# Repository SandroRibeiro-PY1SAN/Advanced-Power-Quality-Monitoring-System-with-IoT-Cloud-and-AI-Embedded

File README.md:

# Advanced-Power-Quality-Monitoring-System-with-IoT-Cloud-and-AI-Embedded
Authors:

Sandro Carneiro Ribeiro

Leonardo de Carvalho Vidal

-------------------------------------------------------------------------------------------------------------------------------------------
Real-time analyzer for managing the electrical variables of an installation connected to a power distributor. This equipment consists of several modular hardware modules and dedicated software.
This project has an electronic interface to support auxiliary voltage (J1) and current (J2) measurement boards, and the microcontroller (U2). The electrical design was developed using KiCad software version 8.0.

The microcontroller used is a 30-pin ESP-WROOM32 from Espressif. This model features the Xtensa® Dual-Core 32-bit LX6 microprocessor, with a maximum clock speed of 240 MHz, 520 KBytes of RAM and 4 MB of Flash memory, a 12-bit ADC, and Wi-Fi and Bluetooth Low Energy (BLE) 4.2 connectivity.

The designed board used 12-bit analog ADC inputs to receive signals from the voltage and current acquisition boards from the mains. Other inputs were reserved for future expansions.

MainBoard SCH:

MainBoard PCB Top:

MainBoard PCB Botton:

VAC Probe:

ACA Probe:

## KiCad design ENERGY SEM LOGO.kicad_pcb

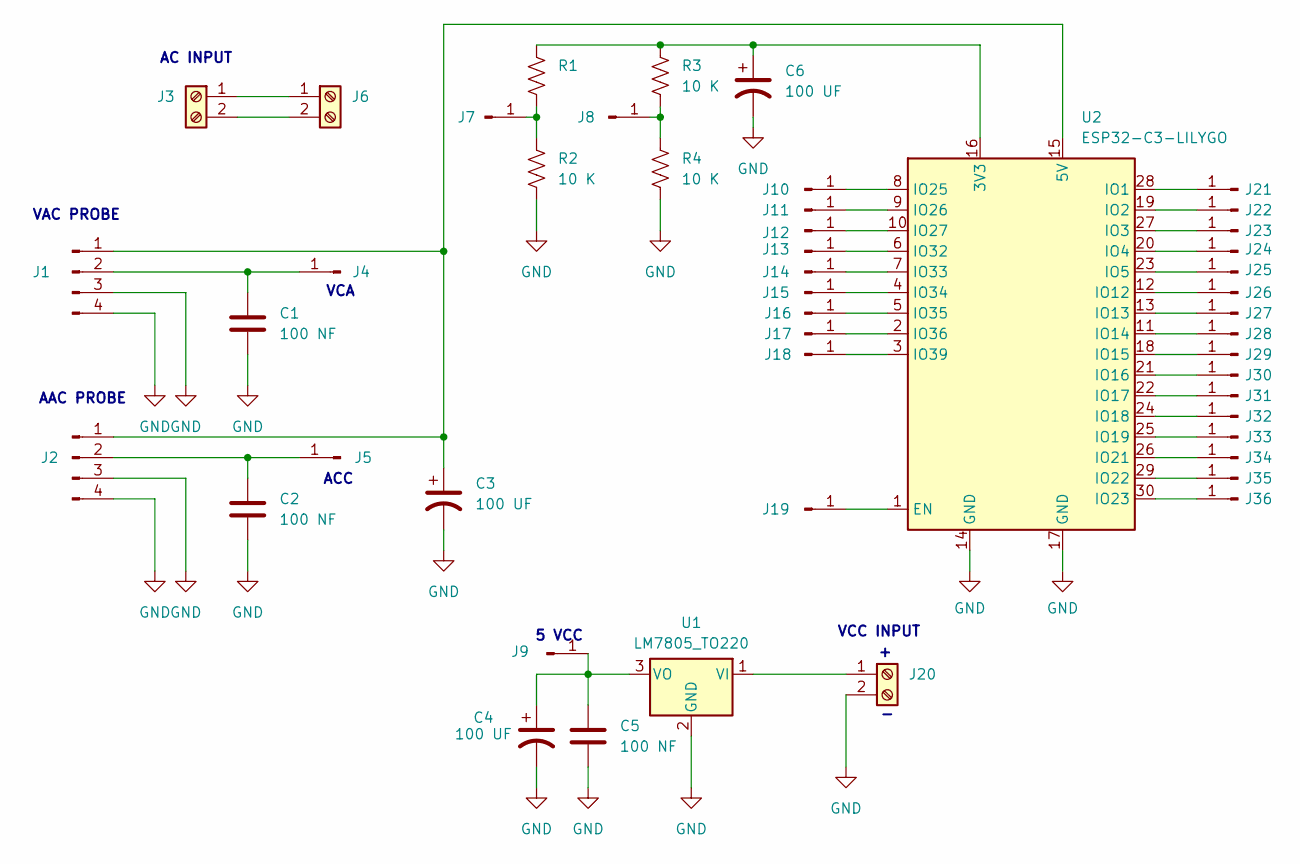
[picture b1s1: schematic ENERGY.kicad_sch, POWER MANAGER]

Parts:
C1, C2, C5: 100 NF; C_Disc_D10.5mm_W5.0mm_P7.50mm
C3, C4, C6: 100 UF; CP_Radial_D8.0mm_P5.00mm
J1, J2: Conn_01x04_Pin; FanPinHeader_1x04_P2.54mm_Vertical
J3, J6, J20: Screw_Terminal_01x02; TestPoint_2Pads_Pitch5.08mm_Drill1.3mm
J4, J5, J7, J8, J9, J10, J11, J12, J13, J14, J15, J16, J17, J18, J19, J21, J22, J23, J24, J25, J26, J27, J28, J29, J30, J31, J32, J33, J34, J35, J36: Conn_01x01_Pin; PinHeader_1x01_P1.00mm_Vertical
R1, R2, R3, R4: 10 K; R_Axial_DIN0411_L9.9mm_D3.6mm_P12.70mm_Horizontal
U1: LM7805_TO220; TO-220-3_Vertical
U2: ESP32-C3-LILYGO; ESP32-C3-DevKitM-1

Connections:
GND: C1.2, C2.2, C3.2, C4.2, C5.2, C6.2, J1.3, J1.4, J2.3, J2.4, J20.2, R2.2, R4.2, U1.2 (GND), U2.14 (GND), U2.17 (GND)
unnamed: C3.1, J1.1, J2.1, U2.15 (5V)
unnamed: C1.1, J1.2, J4.1
unnamed: C2.1, J2.2, J5.1
unnamed: J3.1, J6.1
unnamed: J3.2, J6.2
unnamed: J7.1, R1.2, R2.1
unnamed: J8.1, R3.2, R4.1
unnamed: C4.1, C5.1, J9.1, U1.3 (VO)
unnamed: J10.1, U2.8 (IO25)
unnamed: J11.1, U2.9 (IO26)
unnamed: J12.1, U2.10 (IO27)
unnamed: J13.1, U2.6 (IO32)
unnamed: J14.1, U2.7 (IO33)
unnamed: J15.1, U2.4 (IO34)
unnamed: J16.1, U2.5 (IO35)
unnamed: J17.1, U2.2 (IO36)
unnamed: J18.1, U2.3 (IO39)
unnamed: J19.1, U2.1 (EN)
unnamed: J20.1, U1.1 (VI)
unnamed: J21.1, U2.28 (IO1)
unnamed: J22.1, U2.19 (IO2)
unnamed: J23.1, U2.27 (IO3)
unnamed: J24.1, U2.20 (IO4)
unnamed: J25.1, U2.23 (IO5)
unnamed: J26.1, U2.12 (IO12)
unnamed: J27.1, U2.13 (IO13)
unnamed: J28.1, U2.11 (IO14)
unnamed: J29.1, U2.18 (IO15)
unnamed: J30.1, U2.21 (IO16)
unnamed: J31.1, U2.22 (IO17)
unnamed: J32.1, U2.24 (IO18)
unnamed: J33.1, U2.25 (IO19)
unnamed: J34.1, U2.26 (IO21)
unnamed: J35.1, U2.29 (IO22)
unnamed: J36.1, U2.30 (IO23)
unnamed: C6.1, R1.1, R3.1, U2.16 (3V3)

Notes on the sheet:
5 VCC
ACC
VCC INPUT
VCA
VAC PROBE
AAC PROBE
AC INPUT

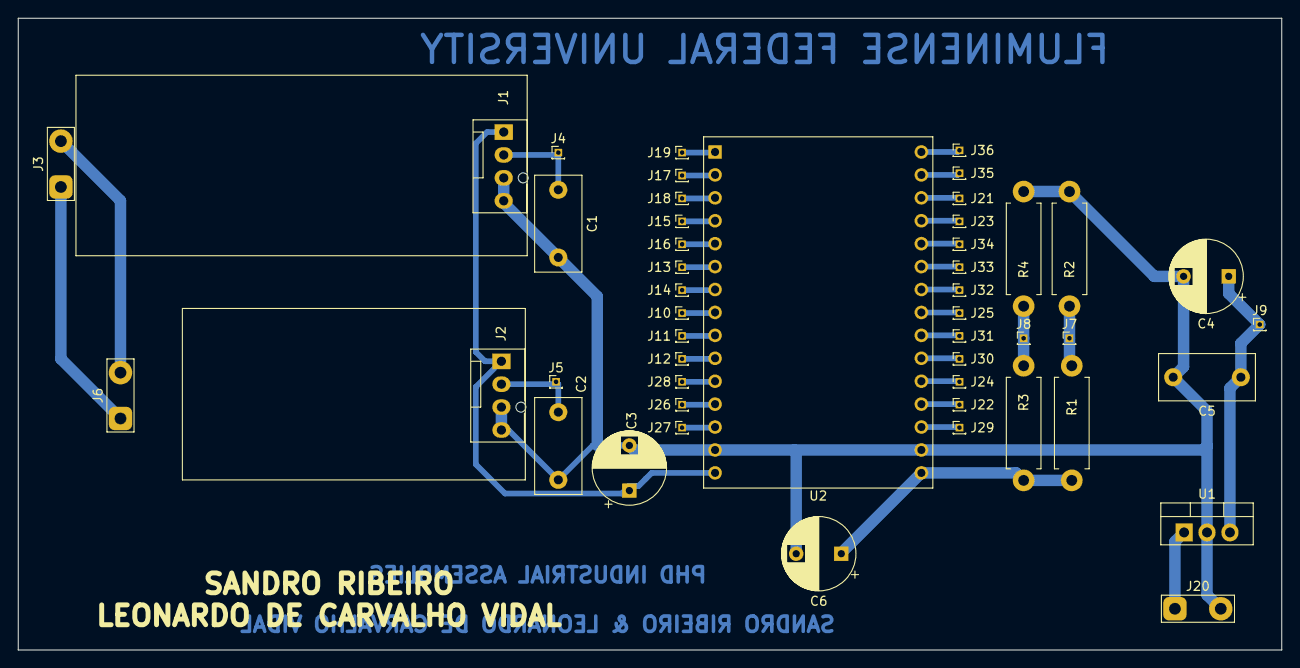
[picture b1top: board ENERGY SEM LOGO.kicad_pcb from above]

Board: 2 copper layers, 140.0 x 70.0 mm, 48 parts (0 on the bottom side), 37 nets.

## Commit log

2026-01-20 ENERGY SEM LOGO.kicad_pro
    ENERGY SEM LOGO.kicad_pro
2026-01-20 ENERGY.kicad_sch
    ENERGY.kicad_sch
2026-01-20 ENERGY SEM LOGO.kicad_pcb
    ENERGY SEM LOGO.kicad_pcb
2026-01-20 VAC PROBE.kicad_pro
    VAC PROBE.kicad_pro
2026-01-20 VAC PROBE.kicad_sch
    VAC PROBE.kicad_sch
2026-01-20 VAC PROBE.kicad_pcb
    VAC PROBE.kicad_pcb
2026-01-20 AAC PROBE.kicad_pro
    AAC PROBE.kicad_pro
2026-01-20 AAC PROBE.kicad_sch
    AAC PROBE.kicad_sch
2026-01-20 AAC PROBE.kicad_pcb
    AAC PROBE.kicad_pcb
2026-01-20 Update README.md
    Schematics and PCB
